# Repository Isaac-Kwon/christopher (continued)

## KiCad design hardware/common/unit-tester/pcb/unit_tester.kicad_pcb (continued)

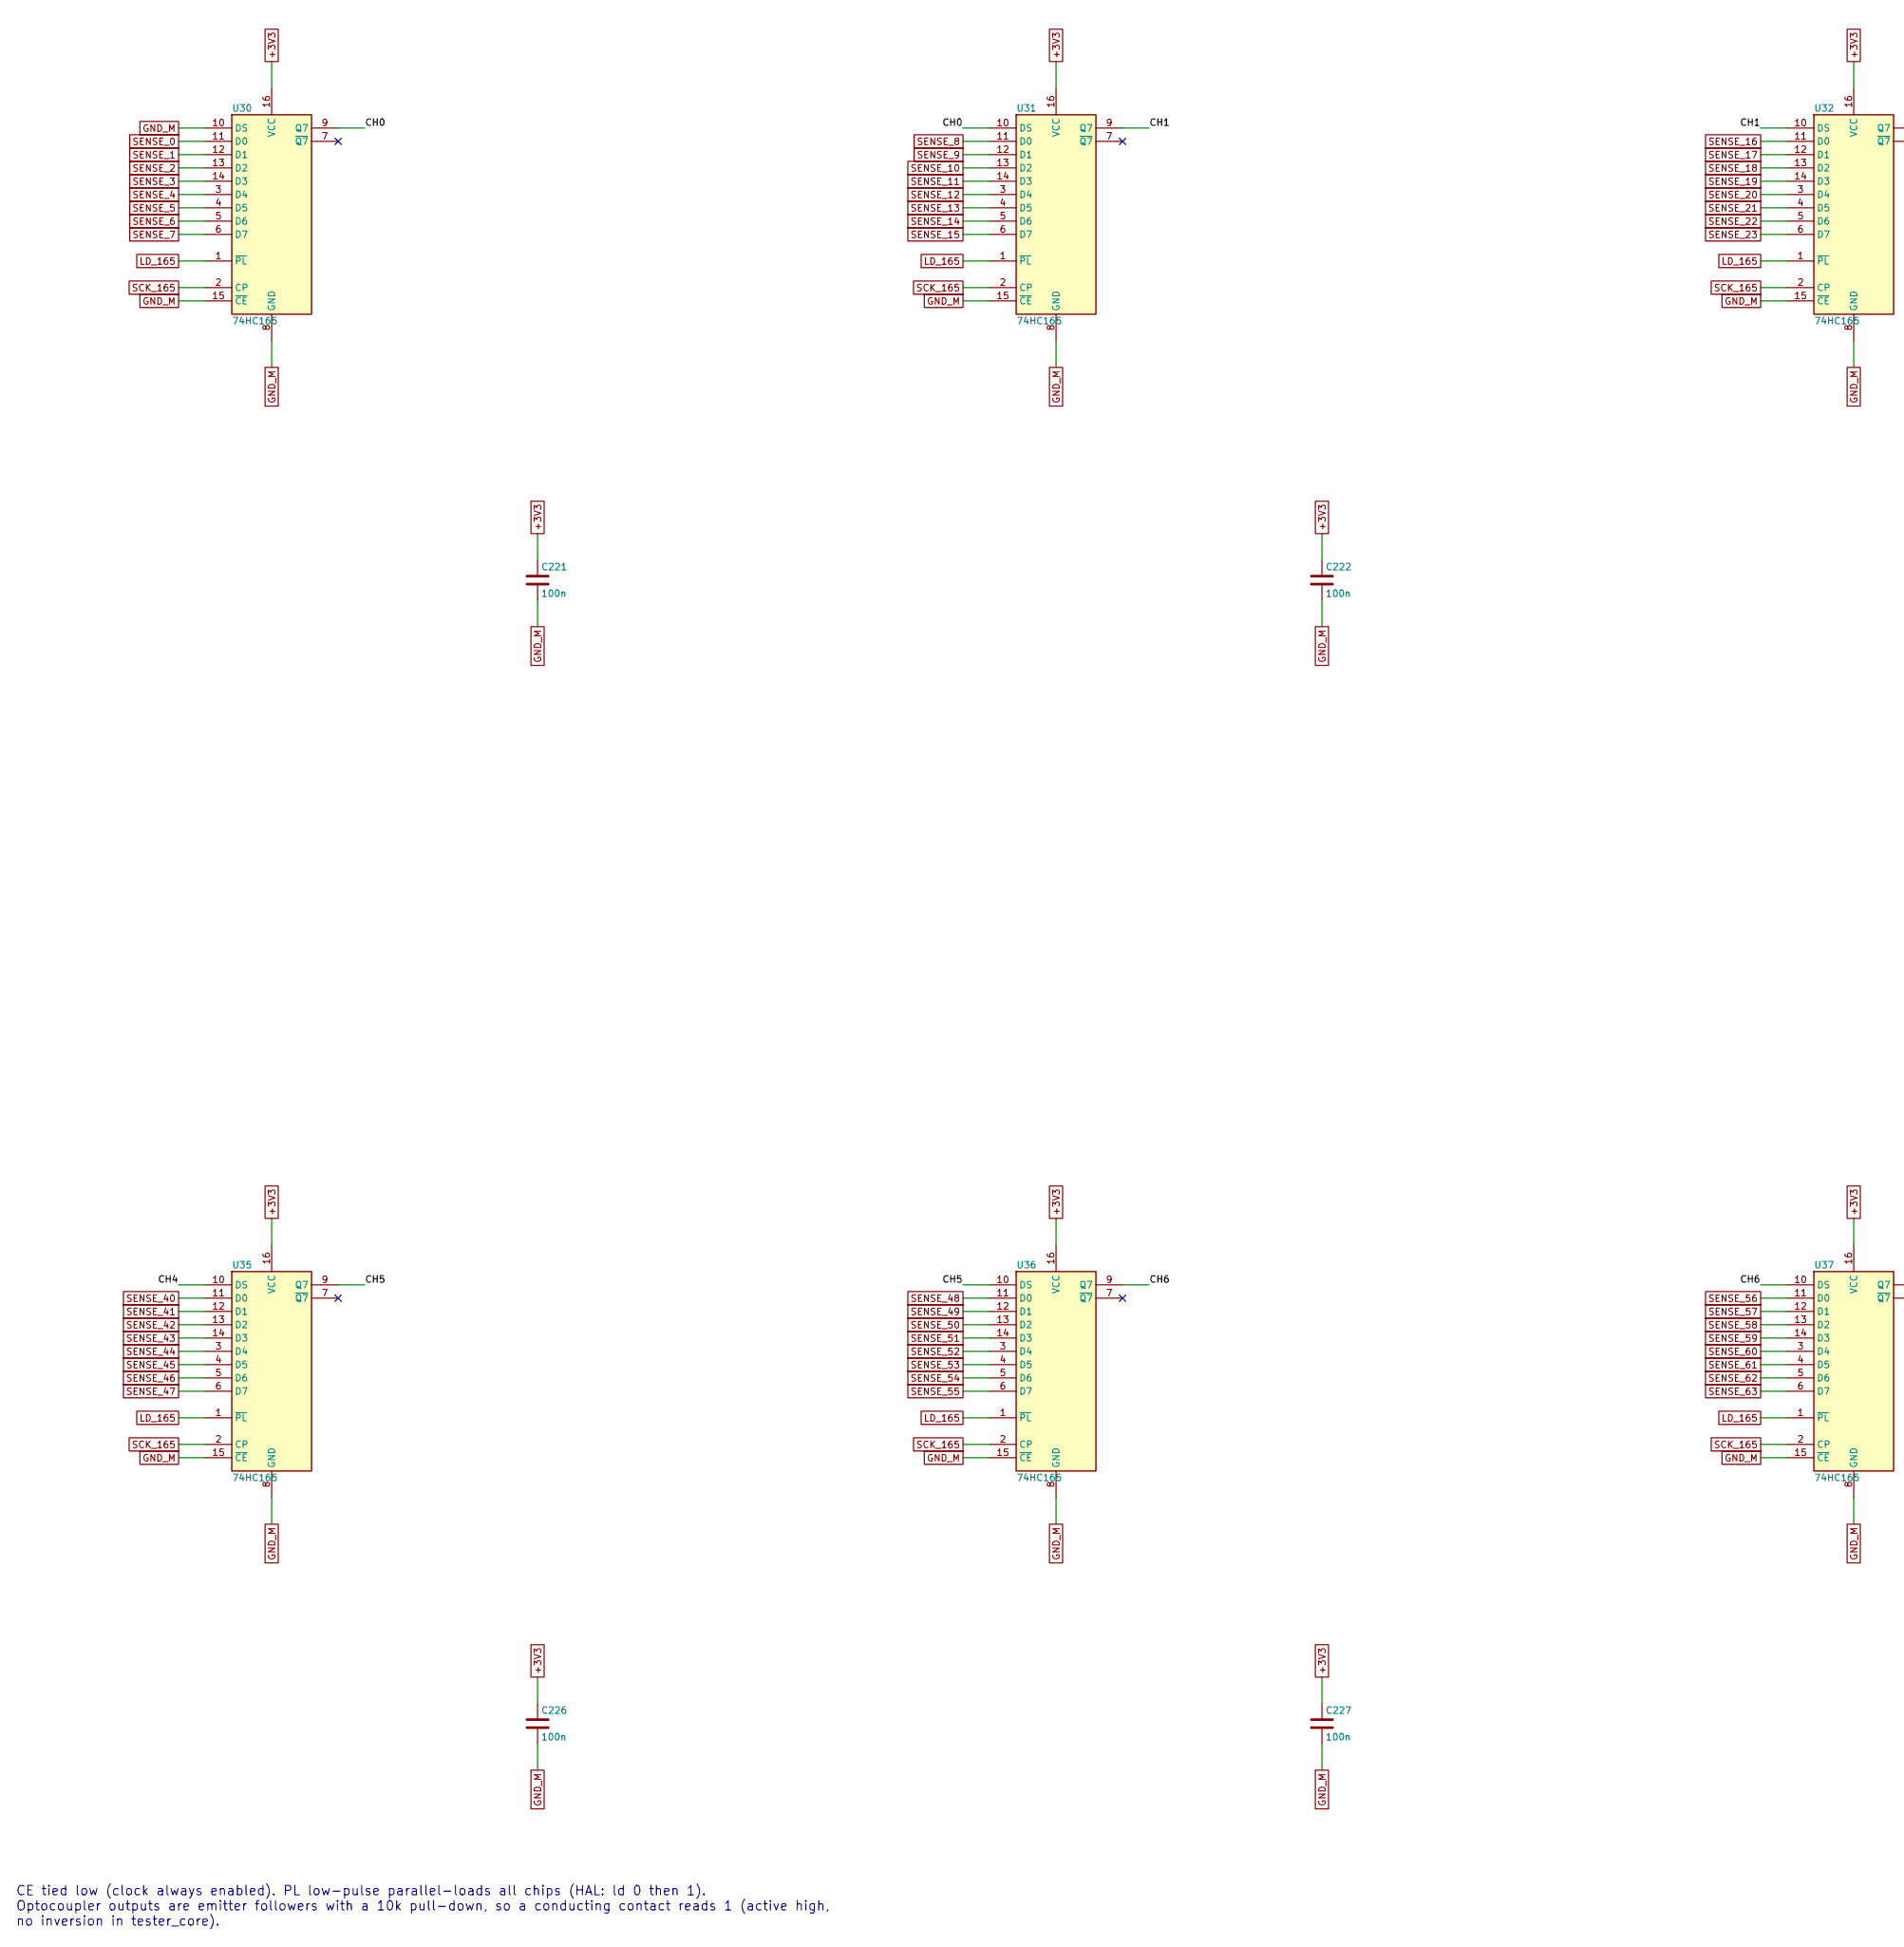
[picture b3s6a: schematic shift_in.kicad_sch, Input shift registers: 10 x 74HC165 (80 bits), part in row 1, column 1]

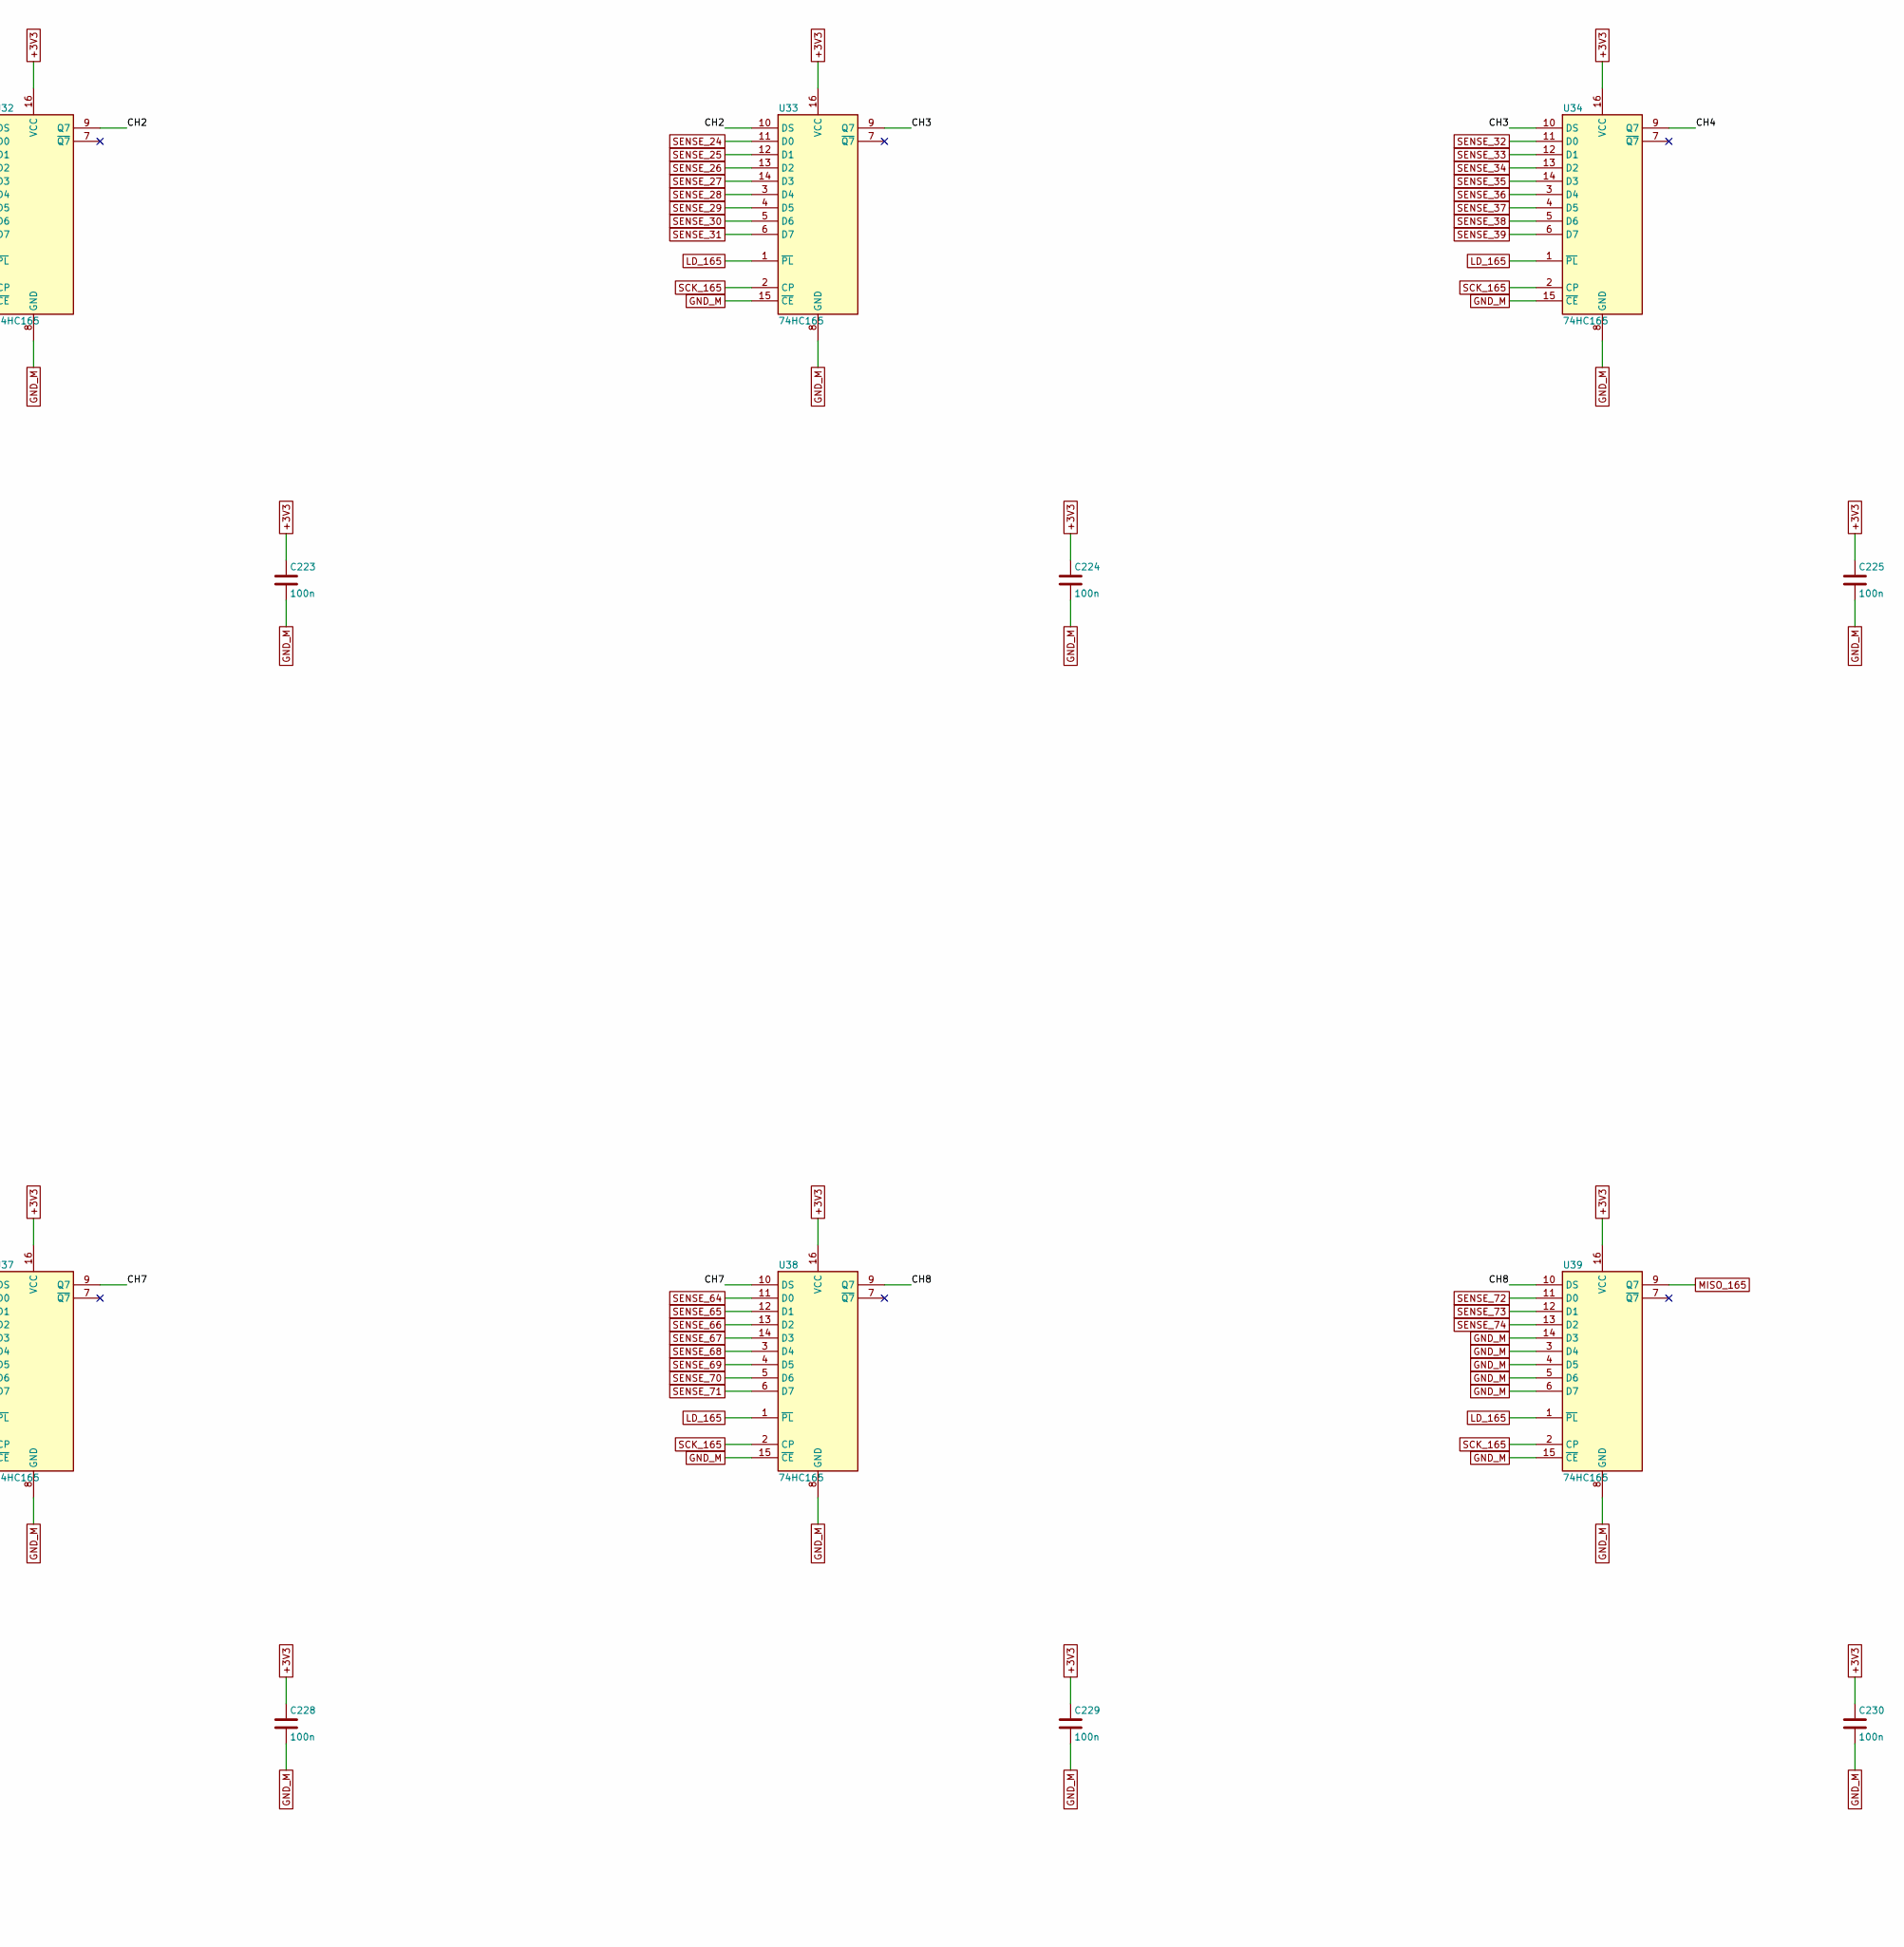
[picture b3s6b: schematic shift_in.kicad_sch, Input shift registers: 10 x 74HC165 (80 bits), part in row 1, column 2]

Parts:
C221, C222, C223, C224, C225, C226, C227, C228, C229, C230: 100n; C_0603_1608Metric
U30, U31, U32, U33, U34, U35, U36, U37, U38, U39: 74HC165; SOIC-16_3.9x9.9mm_P1.27mm

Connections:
+3V3: C221.1, C222.1, C223.1, C224.1, C225.1, C226.1, C227.1, C228.1, C229.1, C230.1, U30.16 (VCC), U31.16 (VCC), U32.16 (VCC), U33.16 (VCC), U34.16 (VCC), U35.16 (VCC), U36.16 (VCC), U37.16 (VCC), U38.16 (VCC), U39.16 (VCC); also elsewhere on the board
/SHIFT_IN/CH0: U30.9 (Q7), U31.10 (DS)
/SHIFT_IN/CH1: U31.9 (Q7), U32.10 (DS)
/SHIFT_IN/CH2: U32.9 (Q7), U33.10 (DS)
/SHIFT_IN/CH3: U33.9 (Q7), U34.10 (DS)
/SHIFT_IN/CH4: U34.9 (Q7), U35.10 (DS)
/SHIFT_IN/CH5: U35.9 (Q7), U36.10 (DS)
/SHIFT_IN/CH6: U36.9 (Q7), U37.10 (DS)
/SHIFT_IN/CH7: U37.9 (Q7), U38.10 (DS)
/SHIFT_IN/CH8: U38.9 (Q7), U39.10 (DS)
GND_M: C221.2, C222.2, C223.2, C224.2, C225.2, C226.2, C227.2, C228.2, C229.2, C230.2, U30.8 (GND), U30.10 (DS), U30.15 (~CE), U31.8 (GND), U31.15 (~CE), U32.8 (GND), U32.15 (~CE), U33.8 (GND), U33.15 (~CE), U34.8 (GND), U34.15 (~CE), U35.8 (GND), U35.15 (~CE), U36.8 (GND), U36.15 (~CE), U37.8 (GND), U37.15 (~CE), U38.8 (GND), U38.15 (~CE), U39.3 (D4), U39.4 (D5), U39.5 (D6), U39.6 (D7), U39.8 (GND), U39.14 (D3), U39.15 (~CE); also elsewhere on the board
LD_165: U30.1 (~PL), U31.1 (~PL), U32.1 (~PL), U33.1 (~PL), U34.1 (~PL), U35.1 (~PL), U36.1 (~PL), U37.1 (~PL), U38.1 (~PL), U39.1 (~PL); also elsewhere on the board
MISO_165: U39.9 (Q7); also elsewhere on the board
SCK_165: U30.2 (CP), U31.2 (CP), U32.2 (CP), U33.2 (CP), U34.2 (CP), U35.2 (CP), U36.2 (CP), U37.2 (CP), U38.2 (CP), U39.2 (CP); also elsewhere on the board
SENSE_0: U30.11 (D0); also elsewhere on the board
SENSE_1: U30.12 (D1); also elsewhere on the board
SENSE_2: U30.13 (D2); also elsewhere on the board
SENSE_3: U30.14 (D3); also elsewhere on the board
SENSE_4: U30.3 (D4); also elsewhere on the board
SENSE_5: U30.4 (D5); also elsewhere on the board
SENSE_6: U30.5 (D6); also elsewhere on the board
SENSE_7: U30.6 (D7); also elsewhere on the board
SENSE_8: U31.11 (D0); also elsewhere on the board
SENSE_9: U31.12 (D1); also elsewhere on the board
SENSE_10: U31.13 (D2); also elsewhere on the board
SENSE_11: U31.14 (D3); also elsewhere on the board
SENSE_12: U31.3 (D4); also elsewhere on the board
SENSE_13: U31.4 (D5); also elsewhere on the board
SENSE_14: U31.5 (D6); also elsewhere on the board
SENSE_15: U31.6 (D7); also elsewhere on the board
SENSE_16: U32.11 (D0); also elsewhere on the board
SENSE_17: U32.12 (D1); also elsewhere on the board
SENSE_18: U32.13 (D2); also elsewhere on the board
SENSE_19: U32.14 (D3); also elsewhere on the board
SENSE_20: U32.3 (D4); also elsewhere on the board
SENSE_21: U32.4 (D5); also elsewhere on the board
SENSE_22: U32.5 (D6); also elsewhere on the board
SENSE_23: U32.6 (D7); also elsewhere on the board
SENSE_24: U33.11 (D0); also elsewhere on the board
SENSE_25: U33.12 (D1); also elsewhere on the board
SENSE_26: U33.13 (D2); also elsewhere on the board
SENSE_27: U33.14 (D3); also elsewhere on the board
SENSE_28: U33.3 (D4); also elsewhere on the board
SENSE_29: U33.4 (D5); also elsewhere on the board
SENSE_30: U33.5 (D6); also elsewhere on the board
SENSE_31: U33.6 (D7); also elsewhere on the board
SENSE_32: U34.11 (D0); also elsewhere on the board
SENSE_33: U34.12 (D1); also elsewhere on the board
SENSE_34: U34.13 (D2); also elsewhere on the board
SENSE_35: U34.14 (D3); also elsewhere on the board
SENSE_36: U34.3 (D4); also elsewhere on the board
SENSE_37: U34.4 (D5); also elsewhere on the board
SENSE_38: U34.5 (D6); also elsewhere on the board
SENSE_39: U34.6 (D7); also elsewhere on the board
SENSE_40: U35.11 (D0); also elsewhere on the board
SENSE_41: U35.12 (D1); also elsewhere on the board
SENSE_42: U35.13 (D2); also elsewhere on the board
SENSE_43: U35.14 (D3); also elsewhere on the board
SENSE_44: U35.3 (D4); also elsewhere on the board
SENSE_45: U35.4 (D5); also elsewhere on the board
SENSE_46: U35.5 (D6); also elsewhere on the board
SENSE_47: U35.6 (D7); also elsewhere on the board
SENSE_48: U36.11 (D0); also elsewhere on the board
SENSE_49: U36.12 (D1); also elsewhere on the board
SENSE_50: U36.13 (D2); also elsewhere on the board
SENSE_51: U36.14 (D3); also elsewhere on the board
SENSE_52: U36.3 (D4); also elsewhere on the board
SENSE_53: U36.4 (D5); also elsewhere on the board
SENSE_54: U36.5 (D6); also elsewhere on the board
SENSE_55: U36.6 (D7); also elsewhere on the board
SENSE_56: U37.11 (D0); also elsewhere on the board
SENSE_57: U37.12 (D1); also elsewhere on the board
SENSE_58: U37.13 (D2); also elsewhere on the board
SENSE_59: U37.14 (D3); also elsewhere on the board
SENSE_60: U37.3 (D4); also elsewhere on the board
SENSE_61: U37.4 (D5); also elsewhere on the board
SENSE_62: U37.5 (D6); also elsewhere on the board
SENSE_63: U37.6 (D7); also elsewhere on the board
SENSE_64: U38.11 (D0); also elsewhere on the board
SENSE_65: U38.12 (D1); also elsewhere on the board
SENSE_66: U38.13 (D2); also elsewhere on the board
SENSE_67: U38.14 (D3); also elsewhere on the board
SENSE_68: U38.3 (D4); also elsewhere on the board
SENSE_69: U38.4 (D5); also elsewhere on the board
SENSE_70: U38.5 (D6); also elsewhere on the board
SENSE_71: U38.6 (D7); also elsewhere on the board
SENSE_72: U39.11 (D0); also elsewhere on the board
SENSE_73: U39.12 (D1); also elsewhere on the board
SENSE_74: U39.13 (D2); also elsewhere on the board

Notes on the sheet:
CE tied low (clock always enabled). PL low-pulse parallel-loads all chips (HAL: ld 0 then 1). Optocoupler outputs are emitter followers with a 10k pull-down, so a conducting contact reads 1 (active high, no inversion in tester_core).

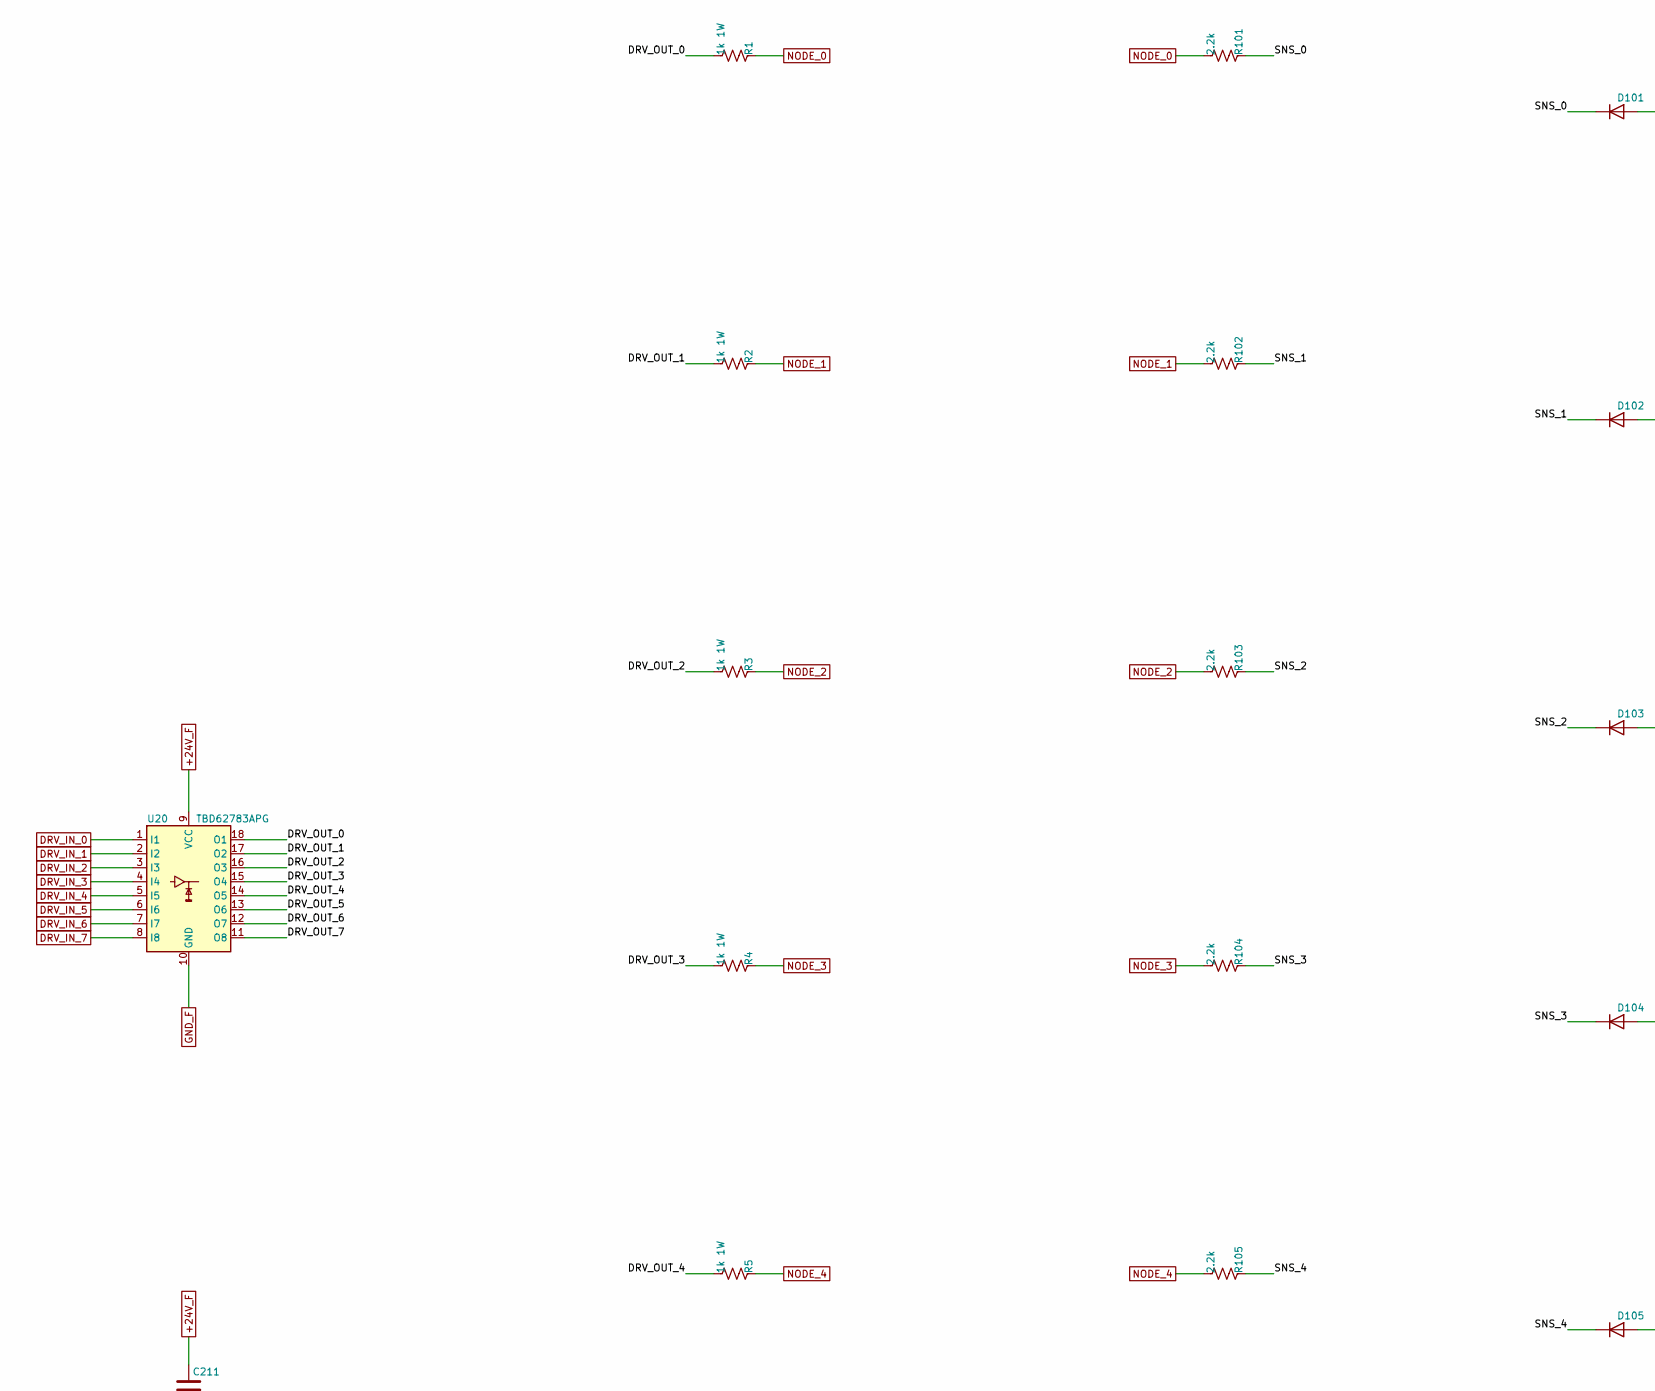
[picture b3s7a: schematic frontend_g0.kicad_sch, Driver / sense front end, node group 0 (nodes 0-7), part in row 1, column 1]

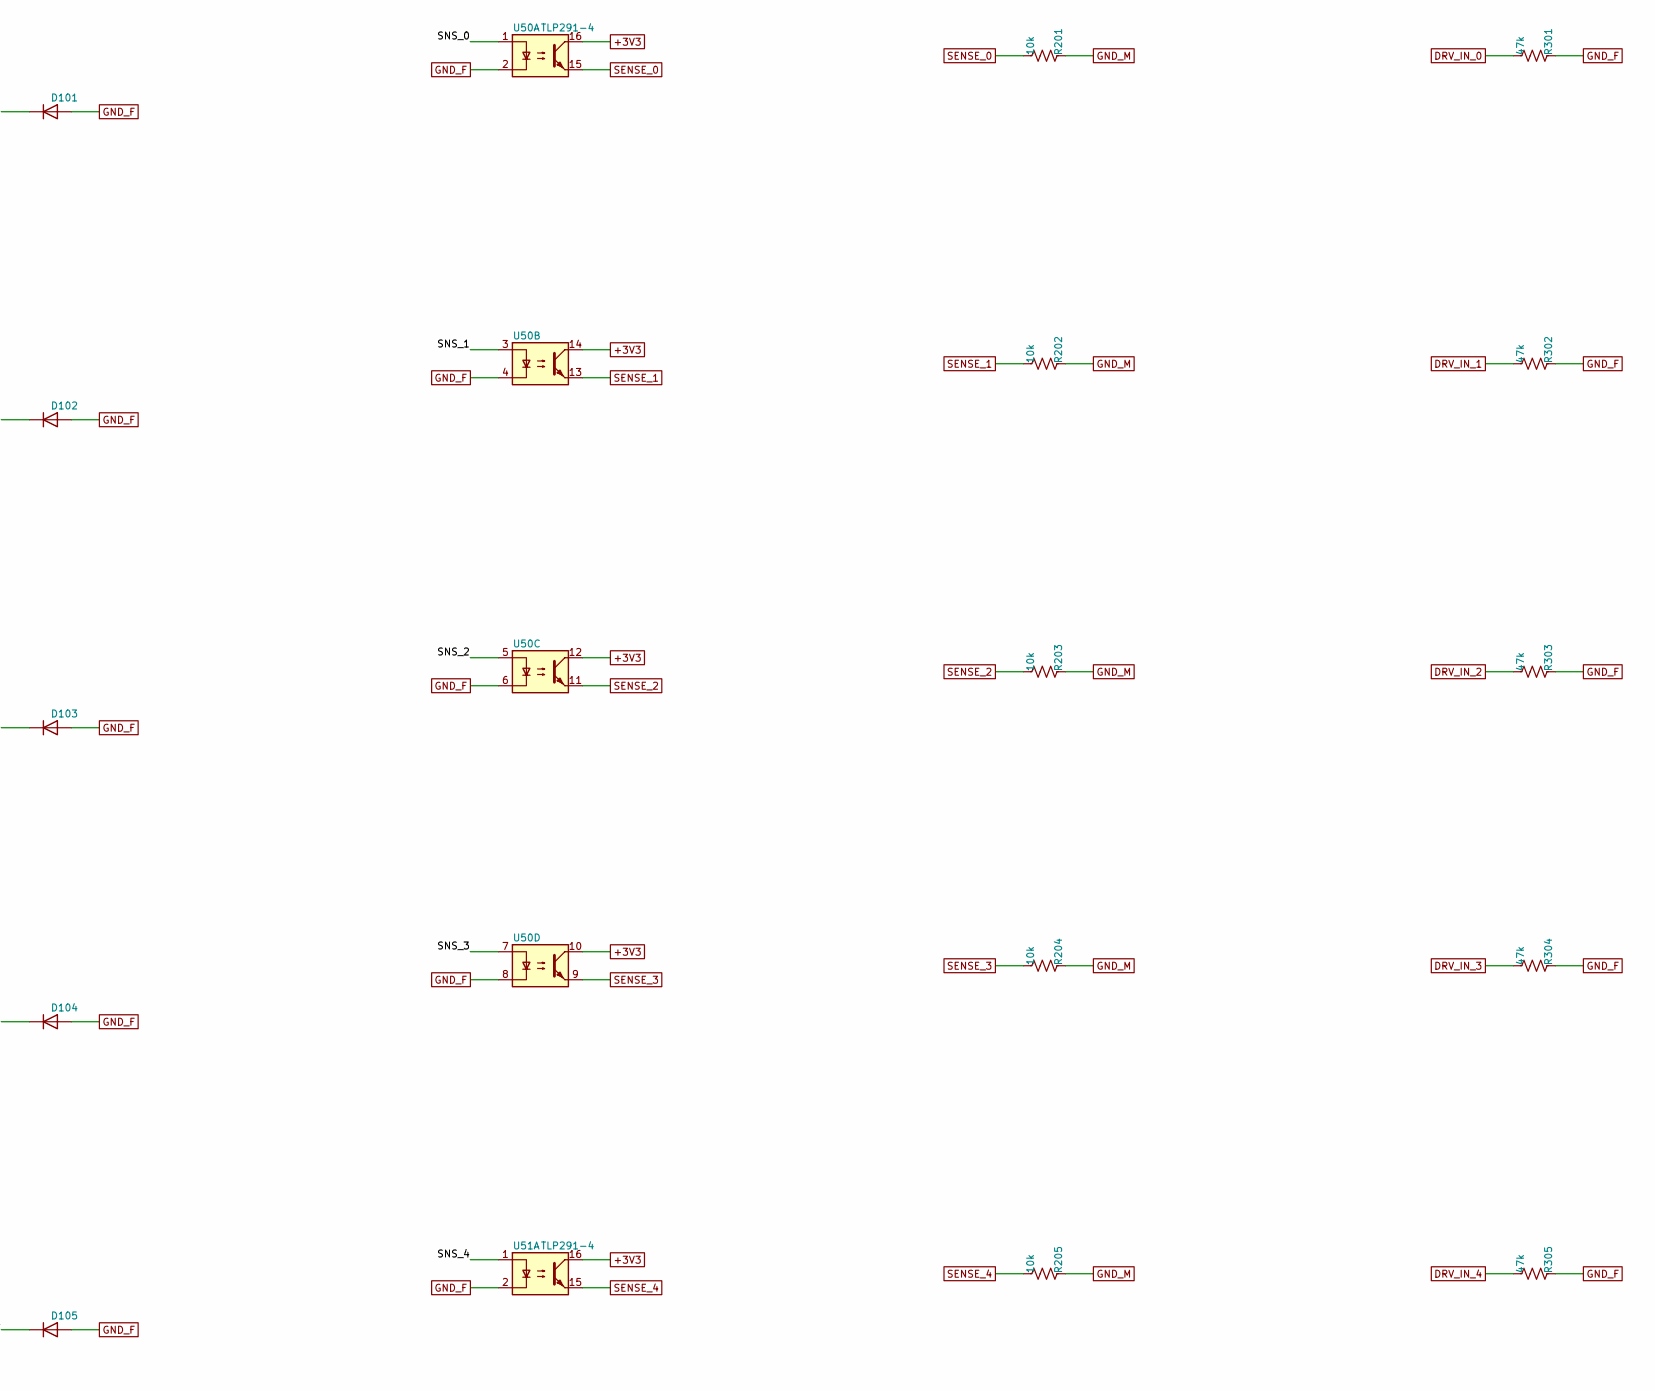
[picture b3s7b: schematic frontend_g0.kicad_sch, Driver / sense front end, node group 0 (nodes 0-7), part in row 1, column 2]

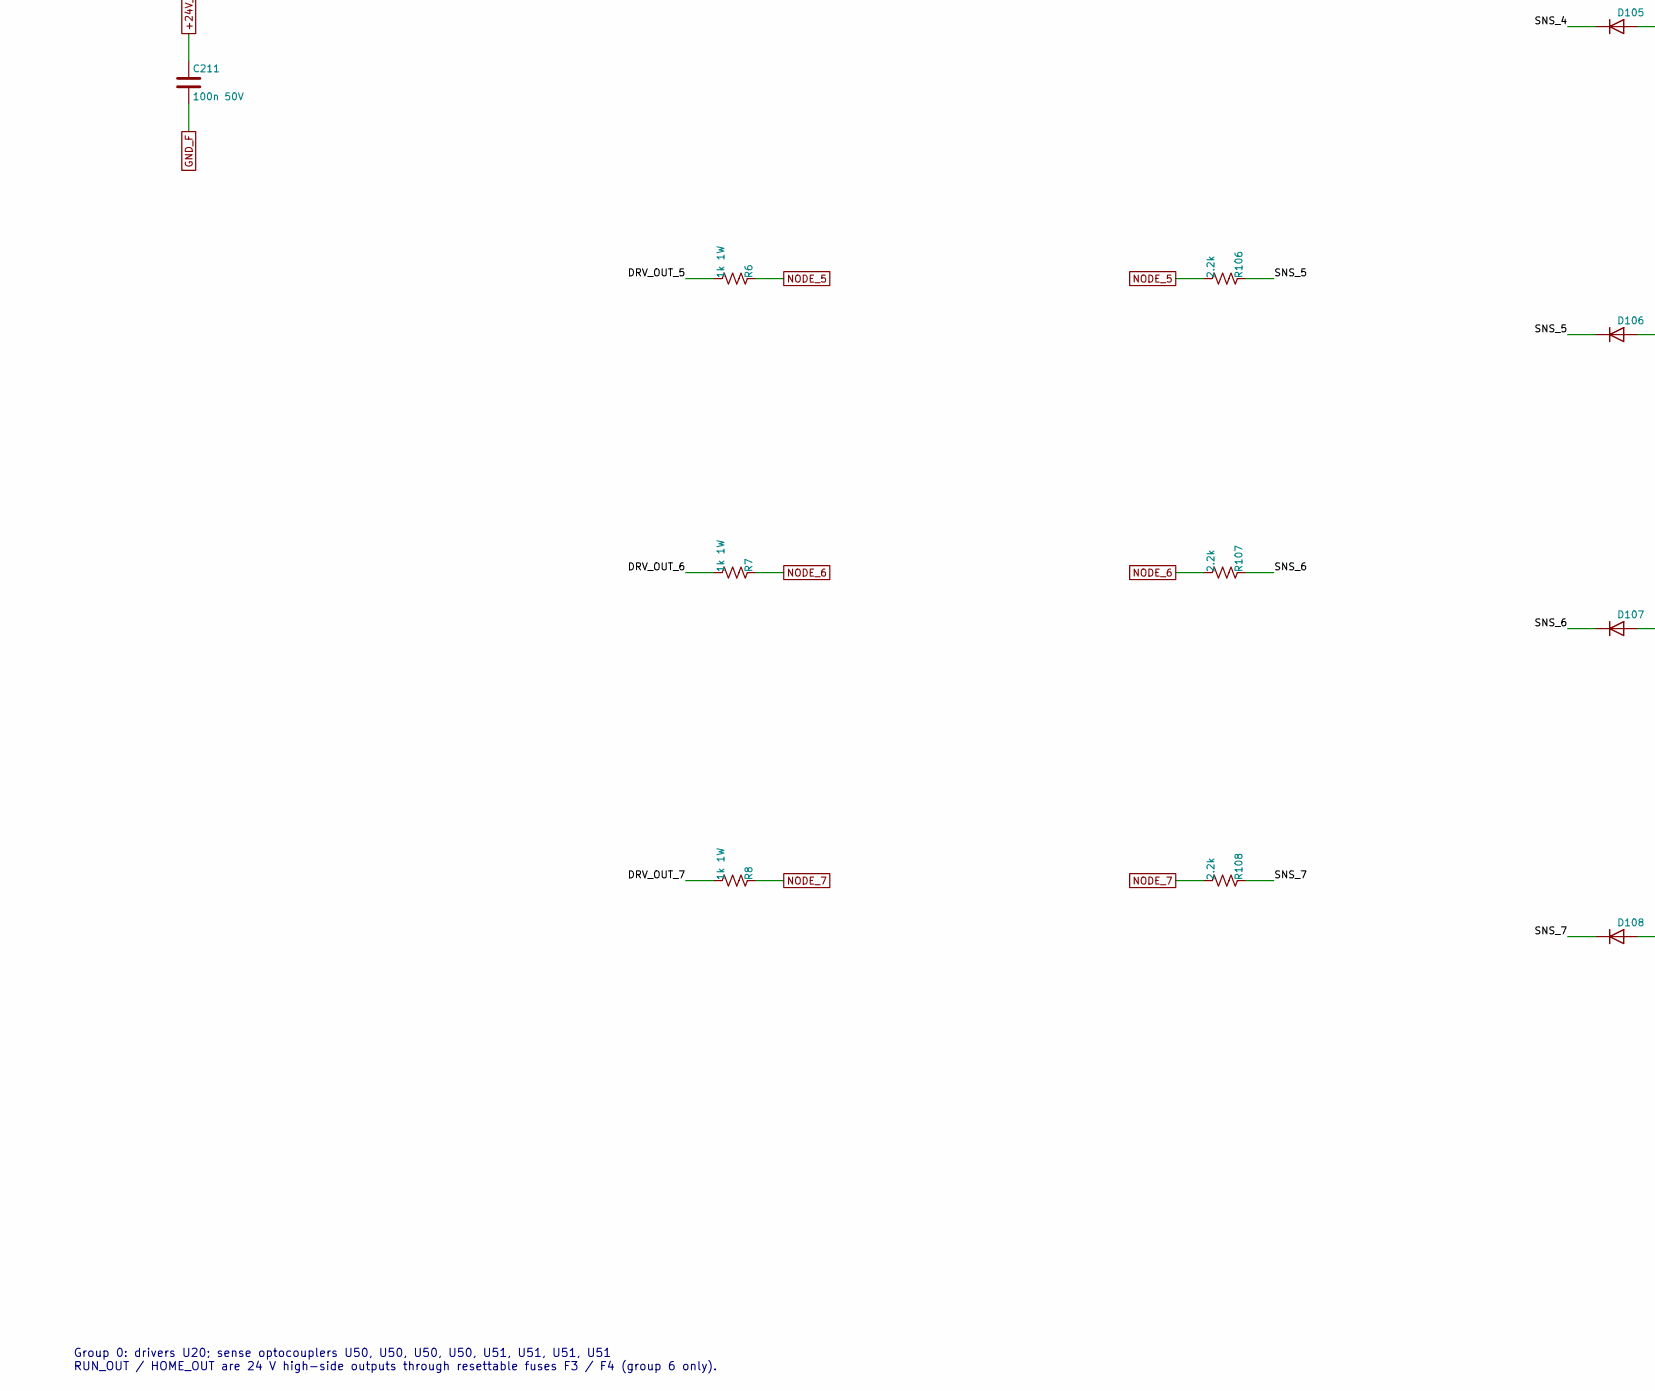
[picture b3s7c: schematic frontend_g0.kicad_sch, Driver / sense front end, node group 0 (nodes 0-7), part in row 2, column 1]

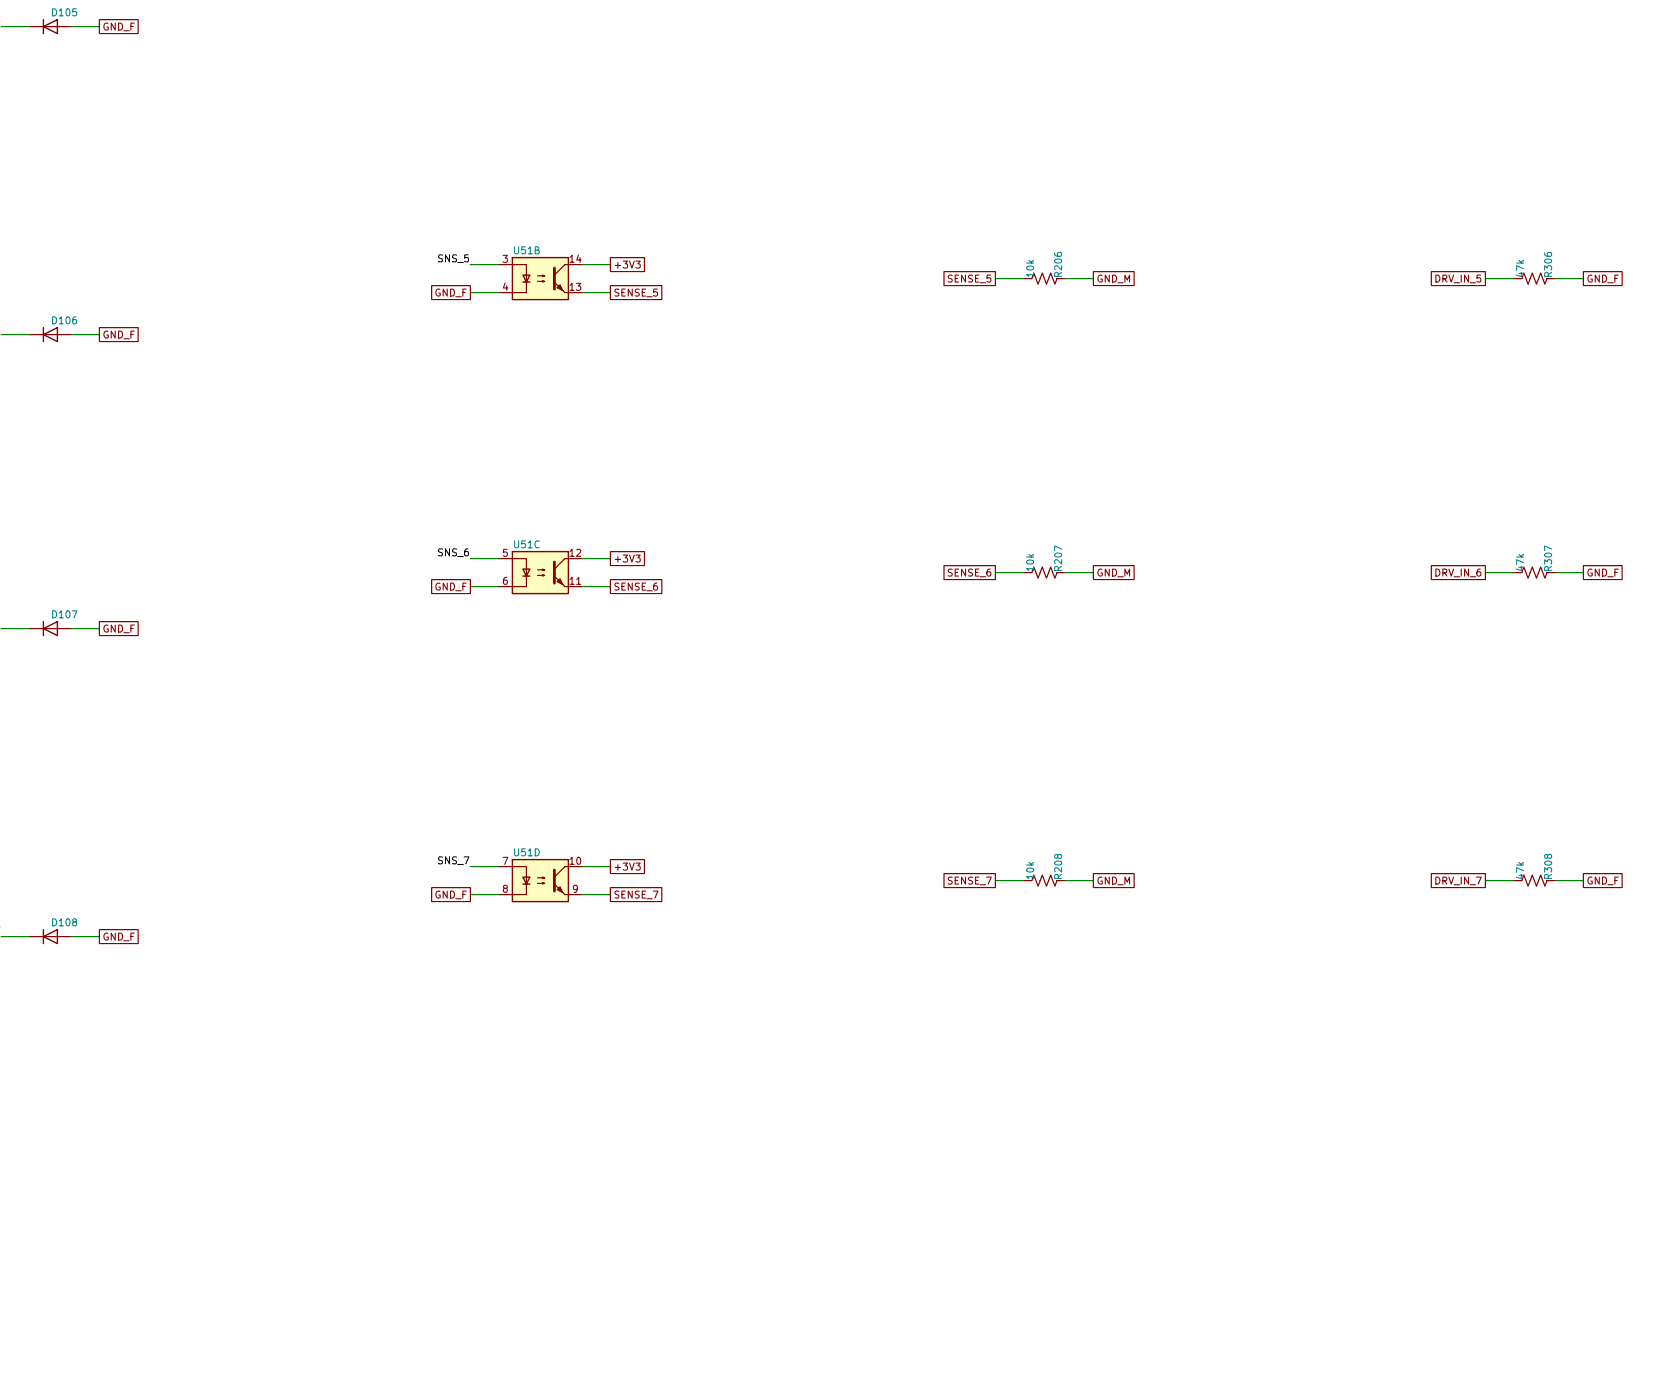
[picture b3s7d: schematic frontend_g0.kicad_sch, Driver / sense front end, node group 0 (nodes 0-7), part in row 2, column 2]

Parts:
C211: 100n 50V; C_0805_2012Metric
D101, D102, D103, D104, D105, D106, D107, D108: 1N4148W; D_SOD-123
R1, R2, R3, R4, R5, R6, R7, R8: 1k 1W; R_2512_6332Metric
R101, R102, R103, R104, R105, R106, R107, R108: 2.2k; R_0603_1608Metric
R201, R202, R203, R204, R205, R206, R207, R208: 10k; R_0603_1608Metric
R301, R302, R303, R304, R305, R306, R307, R308: 47k; R_0603_1608Metric
U20: TBD62783APG; SOIC-18W_7.5x11.6mm_P1.27mm
U50, U51: TLP291-4; SOIC-16_4.55x10.3mm_P1.27mm

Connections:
+3V3: U50.10, U50.12, U50.14, U50.16, U51.10, U51.12, U51.14, U51.16; also elsewhere on the board
+24V_F: C211.1, U20.9 (VCC); also elsewhere on the board
/FRONTEND_G0/DRV_OUT_0: R1.1, U20.18 (O1)
/FRONTEND_G0/DRV_OUT_1: R2.1, U20.17 (O2)
/FRONTEND_G0/DRV_OUT_2: R3.1, U20.16 (O3)
/FRONTEND_G0/DRV_OUT_3: R4.1, U20.15 (O4)
/FRONTEND_G0/DRV_OUT_4: R5.1, U20.14 (O5)
/FRONTEND_G0/DRV_OUT_5: R6.1, U20.13 (O6)
/FRONTEND_G0/DRV_OUT_6: R7.1, U20.12 (O7)
/FRONTEND_G0/DRV_OUT_7: R8.1, U20.11 (O8)
/FRONTEND_G0/SNS_0: D101.1 (K), R101.2, U50.1
/FRONTEND_G0/SNS_1: D102.1 (K), R102.2, U50.3
/FRONTEND_G0/SNS_2: D103.1 (K), R103.2, U50.5
/FRONTEND_G0/SNS_3: D104.1 (K), R104.2, U50.7
/FRONTEND_G0/SNS_4: D105.1 (K), R105.2, U51.1
/FRONTEND_G0/SNS_5: D106.1 (K), R106.2, U51.3
/FRONTEND_G0/SNS_6: D107.1 (K), R107.2, U51.5
/FRONTEND_G0/SNS_7: D108.1 (K), R108.2, U51.7
DRV_IN_0: R301.1, U20.1 (I1); also elsewhere on the board
DRV_IN_1: R302.1, U20.2 (I2); also elsewhere on the board
DRV_IN_2: R303.1, U20.3 (I3); also elsewhere on the board
DRV_IN_3: R304.1, U20.4 (I4); also elsewhere on the board
DRV_IN_4: R305.1, U20.5 (I5); also elsewhere on the board
DRV_IN_5: R306.1, U20.6 (I6); also elsewhere on the board
DRV_IN_6: R307.1, U20.7 (I7); also elsewhere on the board
DRV_IN_7: R308.1, U20.8 (I8); also elsewhere on the board
GND_F: C211.2, D101.2 (A), D102.2 (A), D103.2 (A), D104.2 (A), D105.2 (A), D106.2 (A), D107.2 (A), D108.2 (A), R301.2, R302.2, R303.2, R304.2, R305.2, R306.2, R307.2, R308.2, U20.10 (GND), U50.2, U50.4, U50.6, U50.8, U51.2, U51.4, U51.6, U51.8; also elsewhere on the board
GND_M: R201.2, R202.2, R203.2, R204.2, R205.2, R206.2, R207.2, R208.2; also elsewhere on the board
NODE_0: R1.2, R101.1; also elsewhere on the board
NODE_1: R2.2, R102.1; also elsewhere on the board
NODE_2: R3.2, R103.1; also elsewhere on the board
NODE_3: R4.2, R104.1; also elsewhere on the board
NODE_4: R5.2, R105.1; also elsewhere on the board
NODE_5: R6.2, R106.1; also elsewhere on the board
NODE_6: R7.2, R107.1; also elsewhere on the board
NODE_7: R8.2, R108.1; also elsewhere on the board
SENSE_0: R201.1, U50.15; also elsewhere on the board
SENSE_1: R202.1, U50.13; also elsewhere on the board
SENSE_2: R203.1, U50.11; also elsewhere on the board
SENSE_3: R204.1, U50.9; also elsewhere on the board
SENSE_4: R205.1, U51.15; also elsewhere on the board
SENSE_5: R206.1, U51.13; also elsewhere on the board
SENSE_6: R207.1, U51.11; also elsewhere on the board
SENSE_7: R208.1, U51.9; also elsewhere on the board

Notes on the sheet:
Group 0: drivers U20; sense optocouplers U50, U50, U50, U50, U51, U51, U51, U51 RUN_OUT / HOME_OUT are 24 V high-side outputs through resettable fuses F3 / F4 (group 6 only).
